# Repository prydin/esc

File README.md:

# Brushless ESC Experiment
If you're looking for a functioning, viable ESC, you've come to the wrong place. This is just an experimentation playground.

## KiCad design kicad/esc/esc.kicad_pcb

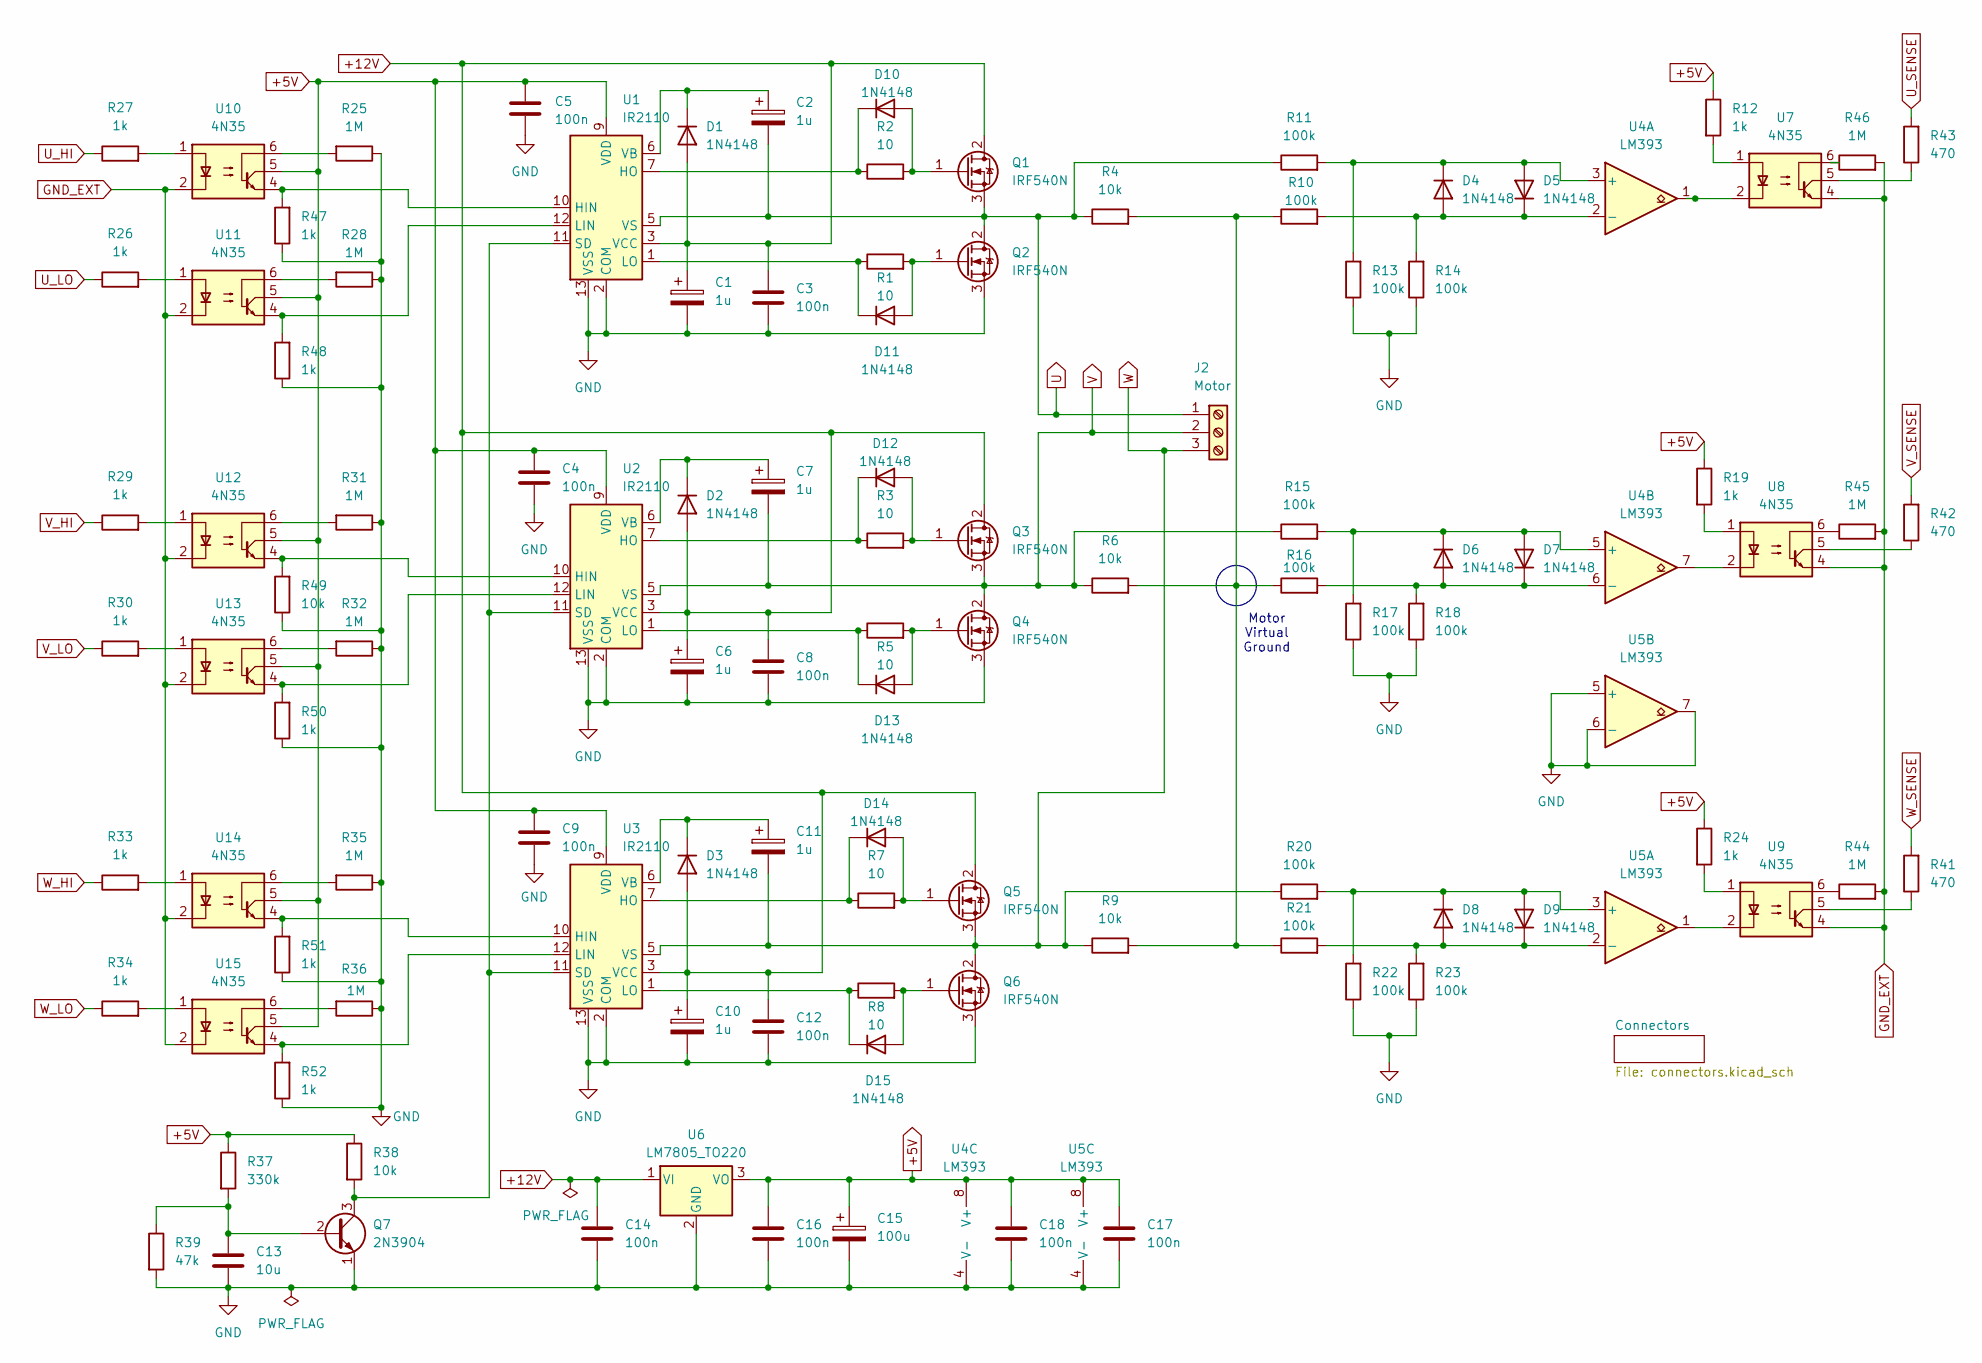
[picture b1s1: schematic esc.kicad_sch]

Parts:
C1, C2, C6, C7, C10, C11: 1u; CP_Radial_D5.0mm_P2.50mm
C3, C4, C5, C8, C9, C12, C14, C16, C17, C18: 100n; C_Disc_D6.0mm_W2.5mm_P5.00mm
C13: 10u; CP_Radial_D5.0mm_P2.50mm
C15: 100u; CP_Radial_D8.0mm_P3.50mm
D1, D2, D3, D4, D5, D6, D7, D8, D9, D10, D11, D12, D13, D14, D15: 1N4148; D_DO-35_SOD27_P7.62mm_Horizontal
J2: Motor; TerminalBlock_MetzConnect_Type059_RT06303HBWC_1x03_P3.50mm_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
Q1, Q2, Q3, Q4, Q5, Q6: IRF540N; TO-220-3_Vertical
Q7: 2N3904; TO-92_Inline
R1, R2, R3, R5, R7, R8: 10; R_Axial_DIN0207_L6.3mm_D2.5mm_P7.62mm_Horizontal
R4, R6, R9, R38: 10k; R_Axial_DIN0207_L6.3mm_D2.5mm_P7.62mm_Horizontal
R10, R11, R13, R14, R15, R16, R17, R18, R20, R21, R22, R23: 100k; R_Axial_DIN0207_L6.3mm_D2.5mm_P7.62mm_Horizontal
R12, R19, R24, R26, R27, R29, R30, R33, R34: 1k; R_Axial_DIN0207_L6.3mm_D2.5mm_P7.62mm_Horizontal
R25, R28, R31, R32, R35, R36, R44, R45, R46: 1M; R_Axial_DIN0204_L3.6mm_D1.6mm_P2.54mm_Vertical
R37: 330k; R_Axial_DIN0207_L6.3mm_D2.5mm_P7.62mm_Horizontal
R39: 47k; R_Axial_DIN0207_L6.3mm_D2.5mm_P7.62mm_Horizontal
R41, R42, R43: 470; R_Axial_DIN0204_L3.6mm_D1.6mm_P2.54mm_Vertical
R47, R48, R50, R51, R52: 1k; R_Axial_DIN0204_L3.6mm_D1.6mm_P2.54mm_Vertical
R49: 10k; R_Axial_DIN0204_L3.6mm_D1.6mm_P2.54mm_Vertical
U1, U2, U3: IR2110; DIP-14_W7.62mm
U4, U5: LM393; DIP-8_W7.62mm
U6: LM7805_TO220; TO-220-3_Vertical
U7, U8, U9, U10, U11, U12, U13, U14, U15: 4N35; DIP-6_W7.62mm

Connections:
+5V: C4.1, C5.1, C9.1, C15.1, C16.1, C17.1, C18.1, R12.1, R19.1, R24.1, R37.1, R38.1, U1.9 (VDD), U2.9 (VDD), U3.9 (VDD), U4.8 (V+), U5.8 (V+), U6.3 (VO), U10.5, U11.5, U12.5, U13.5, U14.5, U15.5
+12V: C1.1, C3.1, C6.1, C8.1, C10.1, C12.1, C14.1, D1.2 (A), D2.2 (A), D3.2 (A), Q1.2 (D), Q3.2 (D), Q5.2 (D), U1.3 (VCC), U2.3 (VCC), U3.3 (VCC), U6.1 (VI); also elsewhere on the board
GND: C1.2, C3.2, C4.2, C5.2, C6.2, C8.2, C9.2, C10.2, C12.2, C13.2, C14.2, C15.2, C16.2, C17.2, C18.2, Q2.3 (S), Q4.3 (S), Q6.3 (S), Q7.1 (E), R13.1, R14.1, R17.1, R18.1, R22.1, R23.1, R25.1, R28.1, R31.1, R32.1, R35.1, R36.1, R39.2, R47.1, R48.1, R49.1, R50.1, R51.1, R52.1, U1.2 (COM), U1.13 (VSS), U2.2 (COM), U2.13 (VSS), U3.2 (COM), U3.13 (VSS), U4.4 (V-), U5.4 (V-), U5.5 (+), U5.6 (-), U5.7, U6.2 (GND); also elsewhere on the board
GND_EXT: R44.2, R45.2, R46.2, U7.4, U8.4, U9.4, U10.2, U11.2, U12.2, U13.2, U14.2, U15.2; also elsewhere on the board
unnamed: C2.1, D1.1 (K), U1.6 (VB)
unnamed: C7.1, D2.1 (K), U2.6 (VB)
unnamed: C11.1, D3.1 (K), U3.6 (VB)
unnamed: D4.2 (A), D5.1 (K), R10.2, R14.2, U4.2 (-)
unnamed: D4.1 (K), D5.2 (A), R11.2, R13.2, U4.3 (+)
unnamed: D6.2 (A), D7.1 (K), R16.2, R18.2, U4.6 (-)
unnamed: D6.1 (K), D7.2 (A), R15.2, R17.2, U4.5 (+)
unnamed: D8.2 (A), D9.1 (K), R21.2, R23.2, U5.2 (-)
unnamed: D8.1 (K), D9.2 (A), R20.2, R22.2, U5.3 (+)
unnamed: D10.2 (A), Q1.1 (G), R2.2
unnamed: D10.1 (K), R2.1, U1.7 (HO)
unnamed: D11.2 (A), Q2.1 (G), R1.2
unnamed: D11.1 (K), R1.1, U1.1 (LO)
unnamed: D12.2 (A), Q3.1 (G), R3.2
unnamed: D12.1 (K), R3.1, U2.7 (HO)
unnamed: D13.2 (A), Q4.1 (G), R5.2
unnamed: D13.1 (K), R5.1, U2.1 (LO)
unnamed: D14.2 (A), Q5.1 (G), R7.2
unnamed: D14.1 (K), R7.1, U3.7 (HO)
unnamed: D15.2 (A), Q6.1 (G), R8.2
unnamed: D15.1 (K), R8.1, U3.1 (LO)
unnamed: C13.1, Q7.2 (B), R37.2, R39.1
unnamed: Q7.3 (C), R38.2, U1.11 (SD), U2.11 (SD), U3.11 (SD)
unnamed: R4.2, R6.2, R9.2, R10.1, R16.1, R21.1
unnamed: R12.2, U7.1
unnamed: R19.2, U8.1
unnamed: R24.2, U9.1
unnamed: R25.2, U10.6
unnamed: R26.2, U11.1
unnamed: R27.2, U10.1
unnamed: R28.2, U11.6
unnamed: R29.2, U12.1
unnamed: R30.2, U13.1
unnamed: R31.2, U12.6
unnamed: R32.2, U13.6
unnamed: R33.2, U14.1
unnamed: R34.2, U15.1
unnamed: R35.2, U14.6
unnamed: R36.2, U15.6
unnamed: R41.1, U9.5
unnamed: R42.1, U8.5
unnamed: R43.1, U7.5
unnamed: R44.1, U9.6
unnamed: R45.1, U8.6
unnamed: R46.1, U7.6
unnamed: R47.2, U1.10 (HIN), U10.4
unnamed: R48.2, U1.12 (LIN), U11.4
unnamed: R49.2, U2.10 (HIN), U12.4
unnamed: R50.2, U2.12 (LIN), U13.4
unnamed: R51.2, U3.10 (HIN), U14.4
unnamed: R52.2, U3.12 (LIN), U15.4
unnamed: U4.1, U7.2
unnamed: U4.7, U8.2
unnamed: U5.1, U9.2
U: C2.2, J2.1, Q1.3 (S), Q2.2 (D), R4.1, R11.1, U1.5 (VS)
U_HI: R27.1; also elsewhere on the board
U_LO: R26.1; also elsewhere on the board
U_SENSE: R43.2; also elsewhere on the board
V: C7.2, J2.2, Q3.3 (S), Q4.2 (D), R6.1, R15.1, U2.5 (VS)
V_HI: R29.1; also elsewhere on the board
V_LO: R30.1; also elsewhere on the board
V_SENSE: R42.2; also elsewhere on the board
W: C11.2, J2.3, Q5.3 (S), Q6.2 (D), R9.1, R20.1, U3.5 (VS)
W_HI: R33.1; also elsewhere on the board
W_LO: R34.1; also elsewhere on the board
W_SENSE: R41.2; also elsewhere on the board

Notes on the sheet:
Motor Virtual Ground

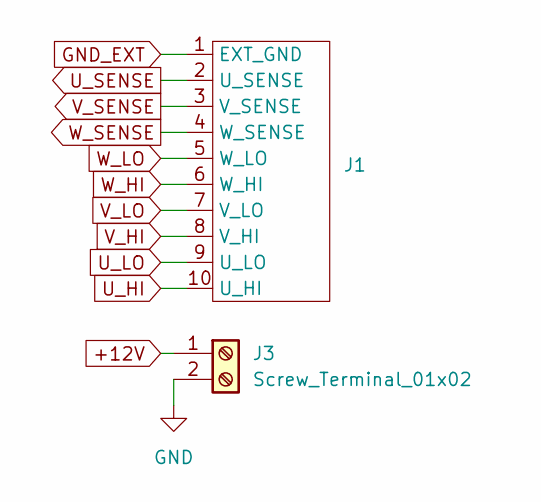
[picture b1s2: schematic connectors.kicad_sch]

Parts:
J1: PinHeader_1x10_P2.54mm_Vertical
J3: Screw_Terminal_01x02; TerminalBlock_4Ucon_1x02_P3.50mm_Vertical

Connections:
+12V: J3.1; also elsewhere on the board
GND: J3.2; also elsewhere on the board
GND_EXT: J1.1 (EXT_GND); also elsewhere on the board
U_HI: J1.10 (U_HI); also elsewhere on the board
U_LO: J1.9 (U_LO); also elsewhere on the board
U_SENSE: J1.2 (U_SENSE); also elsewhere on the board
V_HI: J1.8 (V_HI); also elsewhere on the board
V_LO: J1.7 (V_LO); also elsewhere on the board
V_SENSE: J1.3 (V_SENSE); also elsewhere on the board
W_HI: J1.6 (W_HI); also elsewhere on the board
W_LO: J1.5 (W_LO); also elsewhere on the board
W_SENSE: J1.4 (W_SENSE); also elsewhere on the board

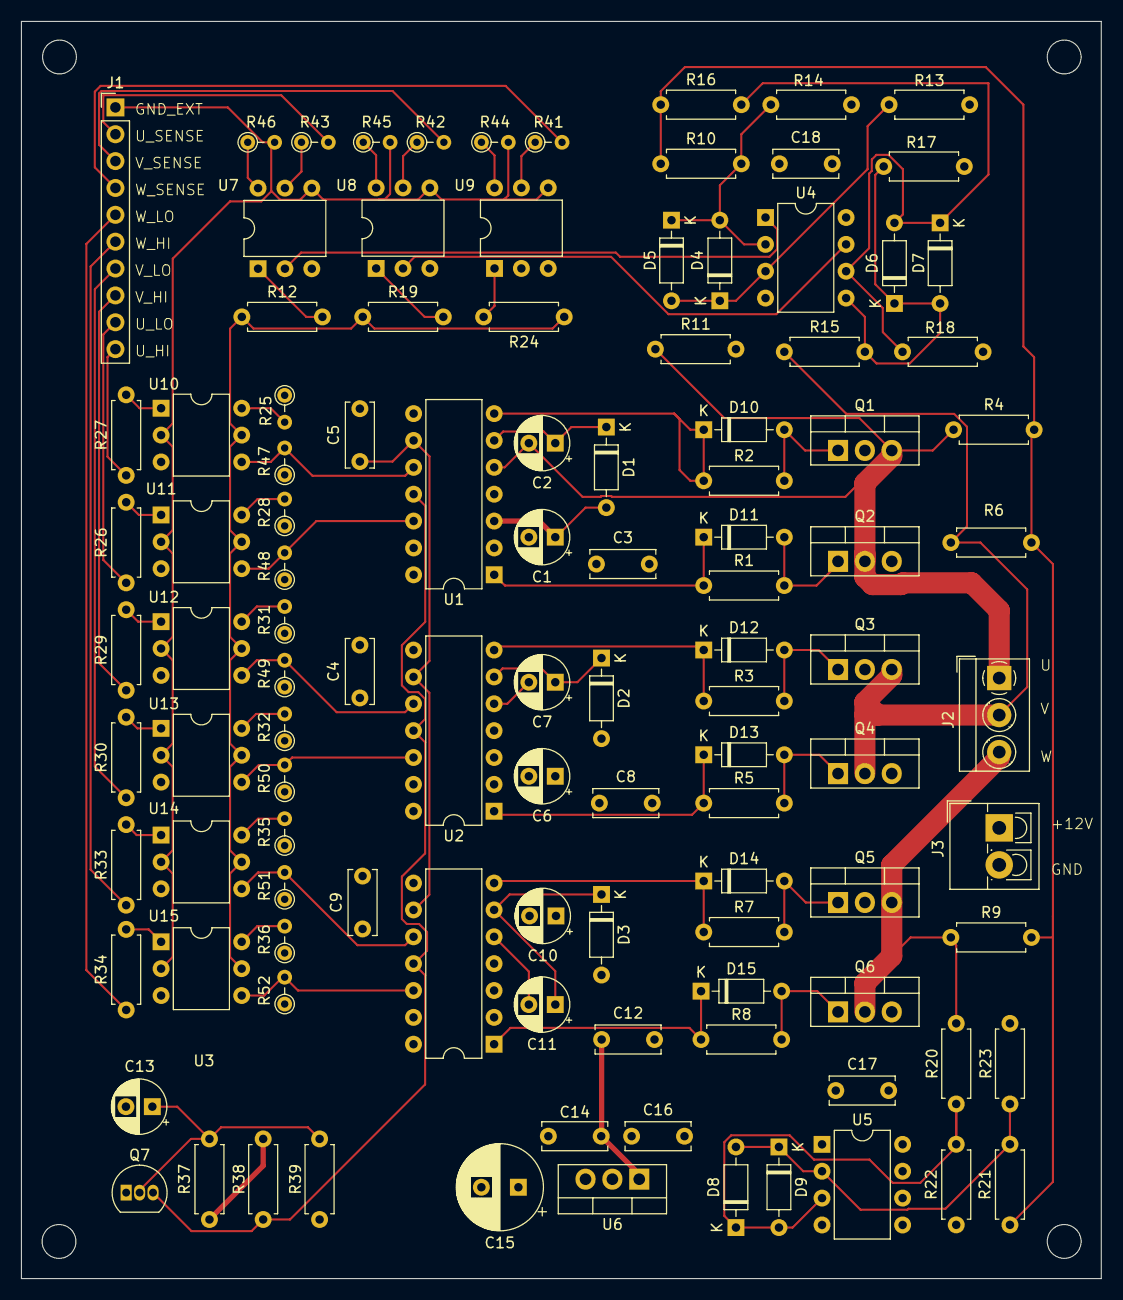
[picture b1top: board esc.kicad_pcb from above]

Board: 4 copper layers, 102.1 x 118.9 mm, 109 parts (0 on the bottom side), 70 nets.

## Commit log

2024-12-27 Complex version of zero detect
2024-12-27 Working zero crossing detection
2024-12-27 Added enable signal
2024-12-29 It's spinning the motor!
2025-01-05 Added driver board
2025-01-10 Added Gerber
2025-01-16 IIR filtering of zero crossing
